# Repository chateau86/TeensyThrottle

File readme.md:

Teensy Throttle Project

4 Throttle Channels. 8 2-way switches (16 buttons). Exponentially-weighted moving average self-tuning for all analog inputs.

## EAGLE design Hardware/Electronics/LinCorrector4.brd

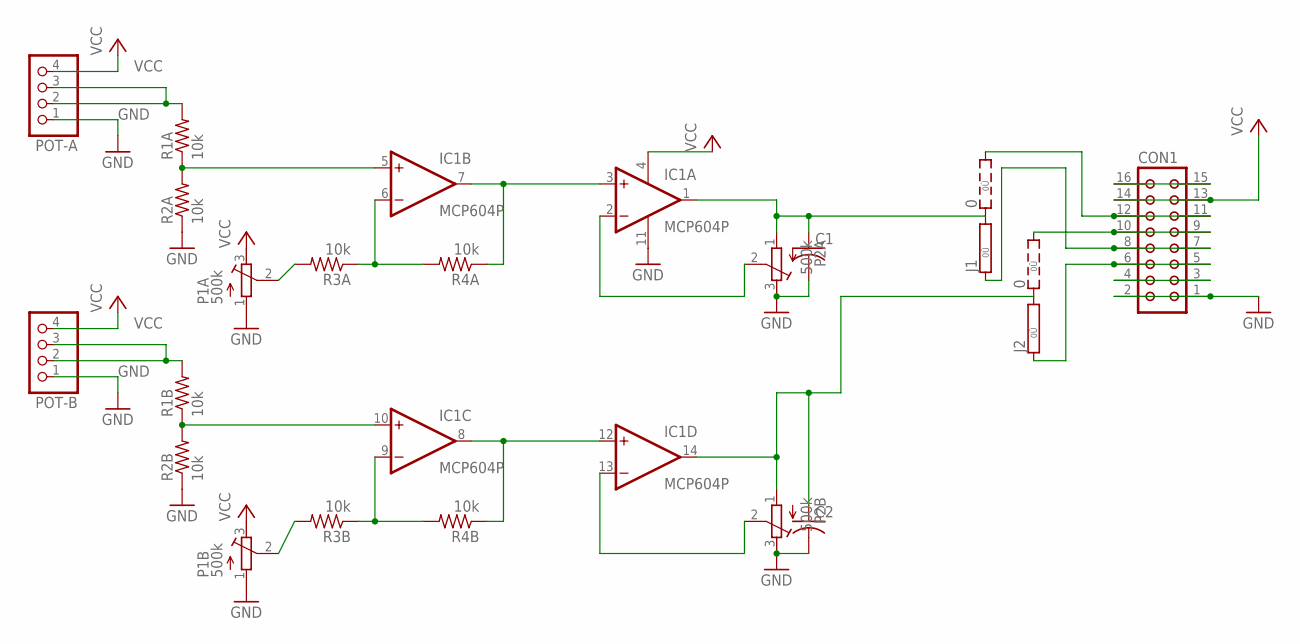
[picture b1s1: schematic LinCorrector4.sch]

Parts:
C1, C2: C-US050-030X075; C050-030X075
CON1: CON16
IC1: MCP604P; DIL14
J1, J2: 0; 0R2/10
P1A, P1B, P2A, P2B: 500k; RTRIM3296W
POT-A: PINHD-1X4/90; 1X04/90
POT-B: PINHD-1X4/90; 1X04/90
R1A, R1B, R2A, R2B, R3A, R3B, R4A, R4B: 10k; 0204/7

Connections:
GND: C1.2, C2.2, CON1.1, CON1.2, IC1.11 (V-), P1A.1 (A), P1B.1 (A), P2A.3 (E), P2B.3 (E), POT-A.1, POT-B.1, R2A.1, R2B.1
unnamed: IC1.5 (+IN), R1A.1, R2A.2
unnamed: POT-A.2, POT-A.3, R1A.2
unnamed: P1A.2 (S), R3A.2
unnamed: IC1.6 (-IN), R3A.1, R4A.2
unnamed: IC1.3 (+IN), IC1.7 (OUT), R4A.1
unnamed: IC1.10 (+IN), R1B.1, R2B.2
unnamed: IC1.2 (-IN), P2A.2 (S)
unnamed: C1.1, IC1.1 (OUT), J1.2, P2A.1 (A)
unnamed: P1B.2 (S), R3B.2
unnamed: IC1.9 (-IN), R3B.1, R4B.2
unnamed: IC1.8 (OUT), IC1.12 (+IN), R4B.1
unnamed: IC1.13 (-IN), P2B.2 (S)
unnamed: C2.1, IC1.14 (OUT), J2.2, P2B.1 (A)
unnamed: POT-B.2, POT-B.3, R1B.2
unnamed: CON1.11, CON1.12, J1.3
unnamed: CON1.9, CON1.10, J2.3
unnamed: CON1.15, CON1.16
unnamed: CON1.3, CON1.4
unnamed: CON1.7, CON1.8, J1.1
unnamed: CON1.5, CON1.6, J2.1
VCC: CON1.13, CON1.14, IC1.4 (V+), P1A.3 (E), P1B.3 (E), POT-A.4, POT-B.4

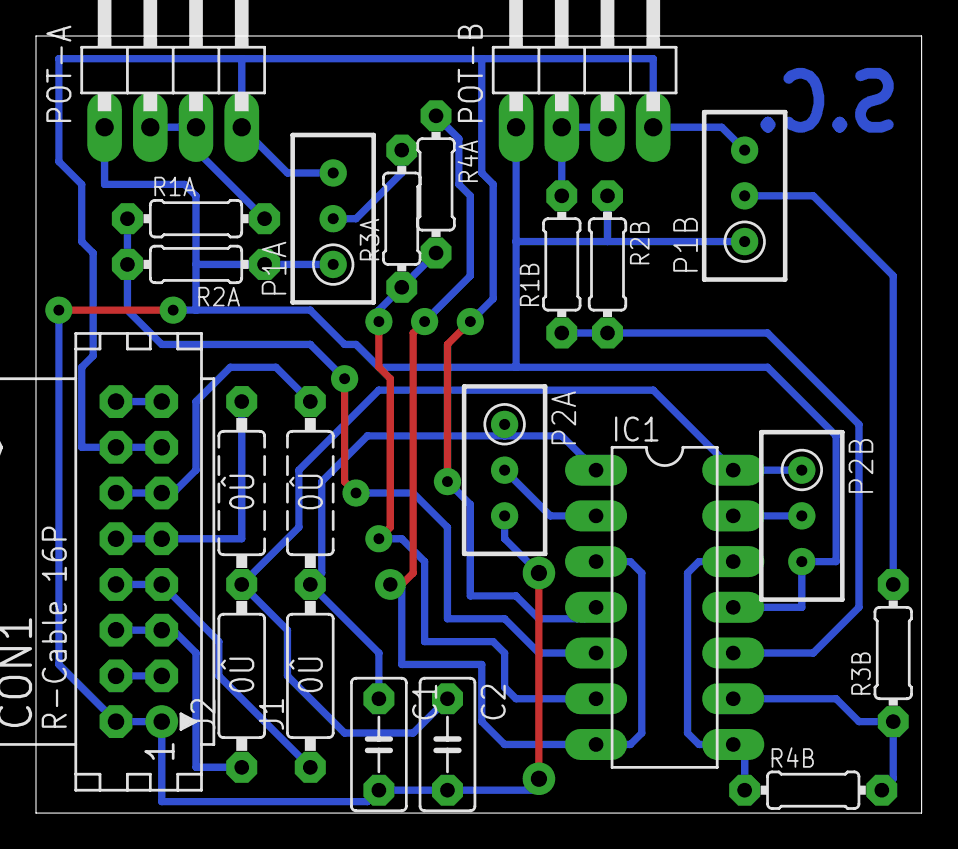
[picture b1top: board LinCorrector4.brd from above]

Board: 2 copper layers, 49.2 x 43.2 mm, 20 parts (0 on the bottom side), 22 nets.

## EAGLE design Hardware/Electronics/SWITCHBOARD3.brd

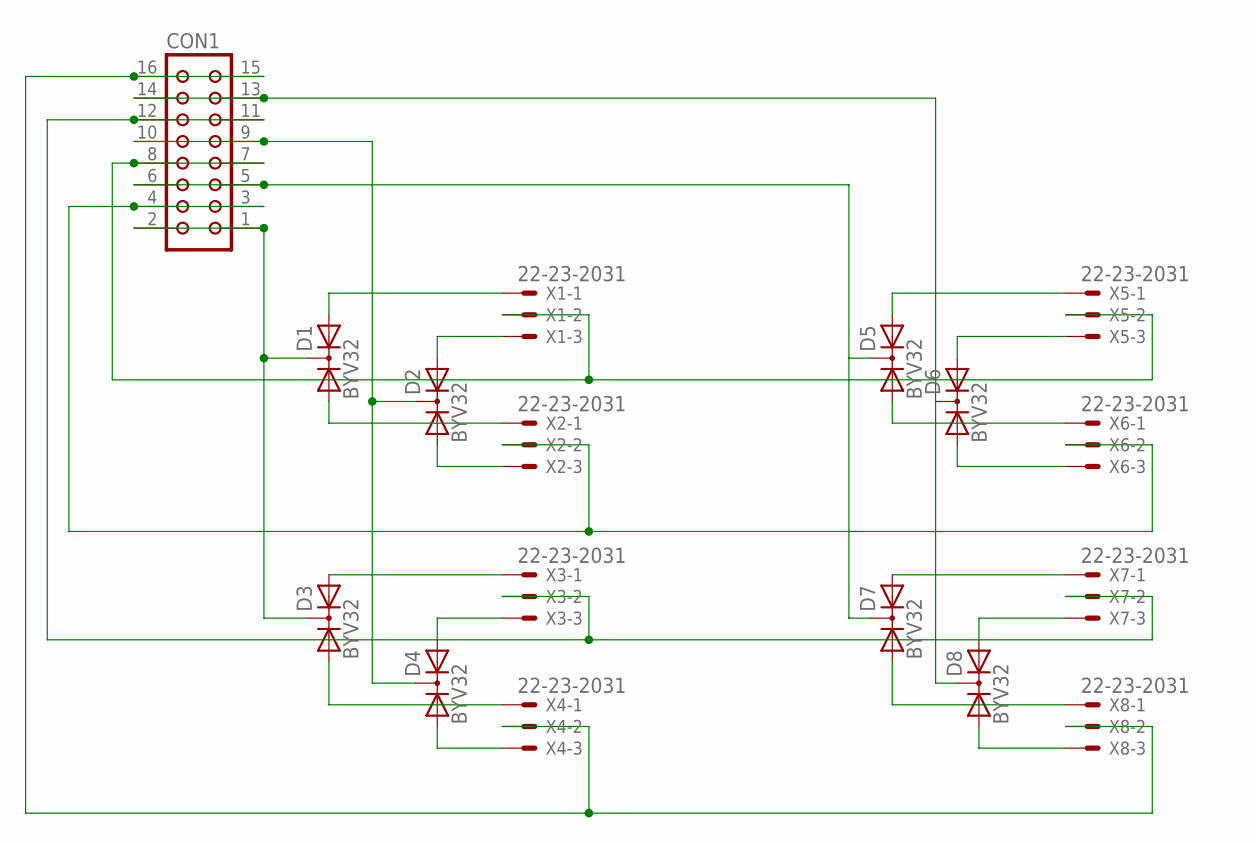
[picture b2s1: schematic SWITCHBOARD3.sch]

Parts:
CON1: CON16
D1, D2, D3, D4, D5, D6, D7, D8: BYV32; TO220ABS
X1, X2, X3, X4, X5, X6, X7, X8: 22-23-2031

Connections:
unnamed: D1.A2, X1.1
unnamed: D2.A2, X1.3
unnamed: D4.A1, X4.3
unnamed: D4.A2, X3.3
unnamed: D1.A1, X2.1
unnamed: D2.A1, X2.3
unnamed: D3.A2, X3.1
unnamed: D3.A1, X4.1
unnamed: D5.A2, X5.1
unnamed: D5.A1, X6.1
unnamed: D6.A2, X5.3
unnamed: D6.A1, X6.3
unnamed: D7.A2, X7.1
unnamed: D7.A1, X8.1
unnamed: D8.A2, X7.3
unnamed: D8.A1, X8.3
unnamed: CON1.9, CON1.10, D2.C, D4.C
unnamed: CON1.1, CON1.2, D1.C, D3.C
unnamed: CON1.13, CON1.14, D6.C, D8.C
unnamed: CON1.7, CON1.8, X1.2, X5.2
unnamed: CON1.3, CON1.4, X2.2, X6.2
unnamed: CON1.11, CON1.12, X3.2, X7.2
unnamed: CON1.15, CON1.16, X4.2, X8.2
unnamed: CON1.5, CON1.6, D5.C, D7.C

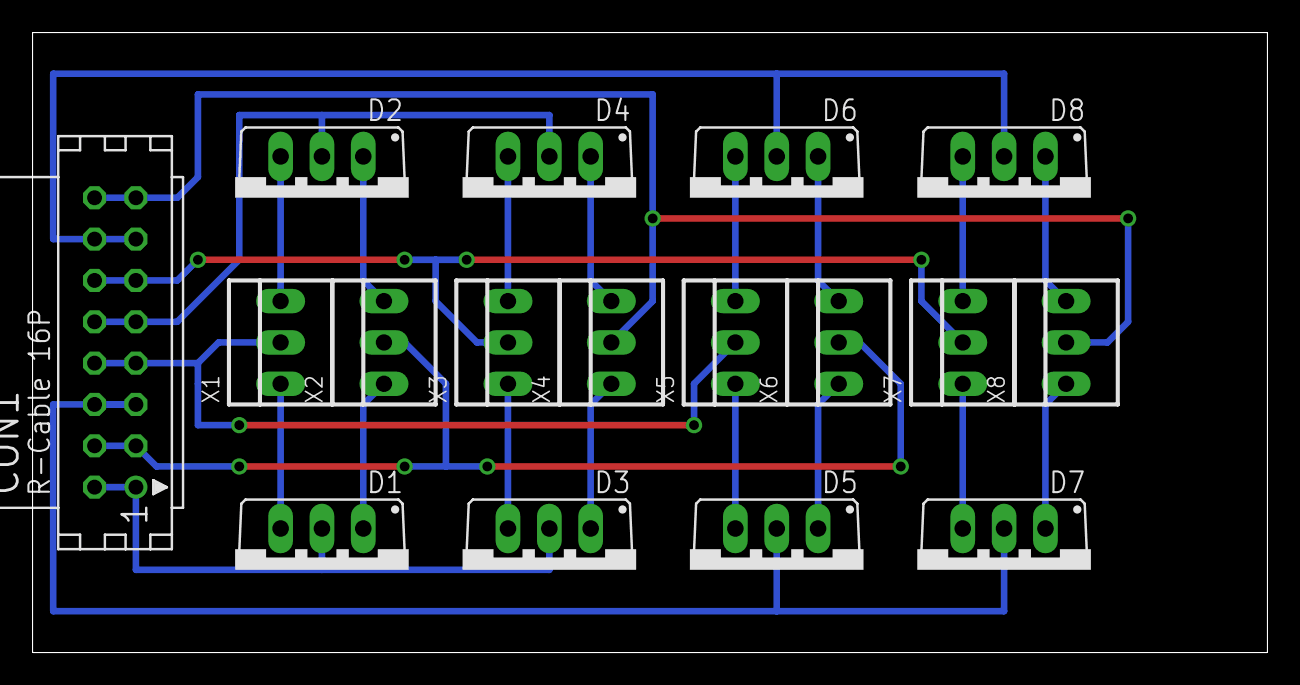
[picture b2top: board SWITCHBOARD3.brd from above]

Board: 2 copper layers, 75.9 x 38.1 mm, 17 parts (0 on the bottom side), 24 nets.

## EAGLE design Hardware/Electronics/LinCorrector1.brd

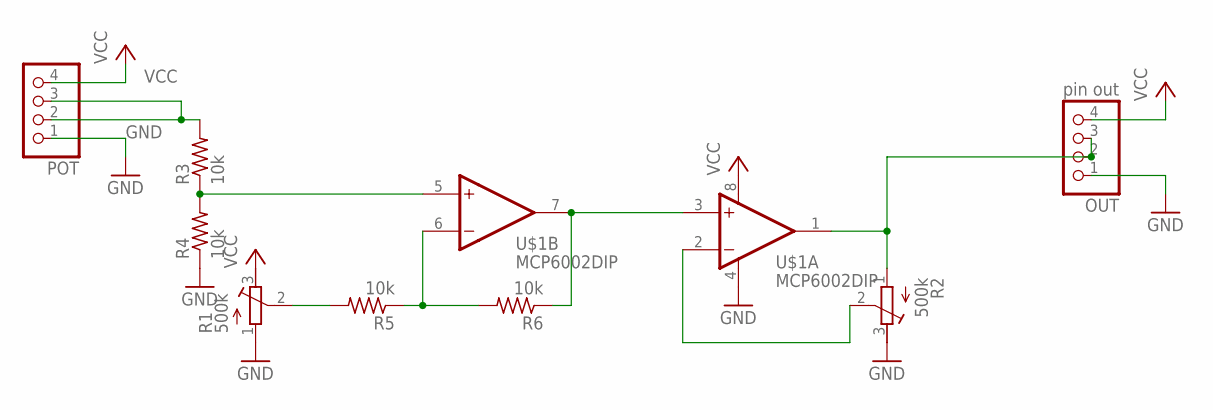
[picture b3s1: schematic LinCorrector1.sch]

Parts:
OUT: pin out; 1X04/90
POT: PINHD-1X4/90; 1X04/90
R1, R2: 500k; RTRIM3296W
R3, R4, R5, R6: 10k; 0204/7
U$1: MCP6002DIP; DIP-8

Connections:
GND: OUT.1, POT.1, R1.1 (A), R2.3 (E), R4.1, U$1.4 (V-)
unnamed: R3.1, R4.2, U$1.5 (+IN)
unnamed: POT.2, POT.3, R3.2
unnamed: R1.2 (S), R5.2
unnamed: R5.1, R6.2, U$1.6 (-IN)
unnamed: R6.1, U$1.3 (+IN), U$1.7 (OUT)
unnamed: R2.2 (S), U$1.2 (-IN)
unnamed: OUT.2, OUT.3, R2.1 (A), U$1.1 (OUT)
VCC: OUT.4, POT.4, R1.3 (E), U$1.8 (V+)

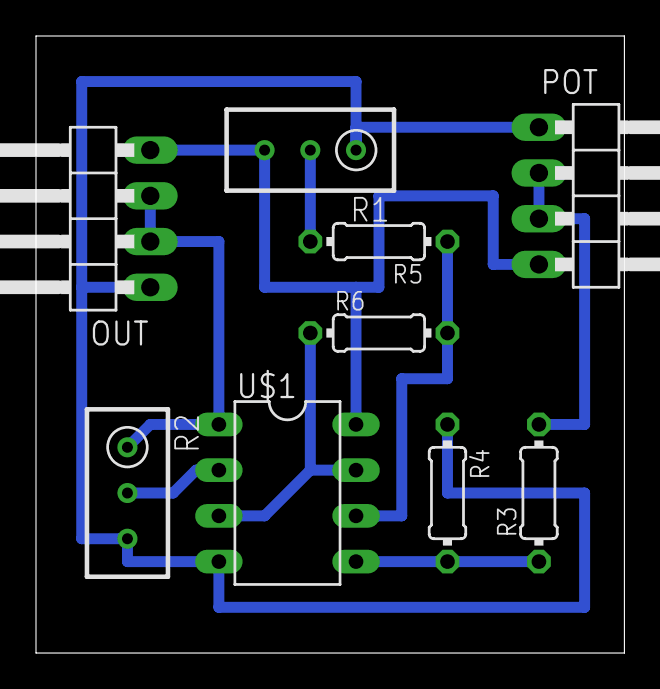
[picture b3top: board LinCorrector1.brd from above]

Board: 2 copper layers, 32.7 x 34.3 mm, 9 parts (0 on the bottom side), 9 nets.

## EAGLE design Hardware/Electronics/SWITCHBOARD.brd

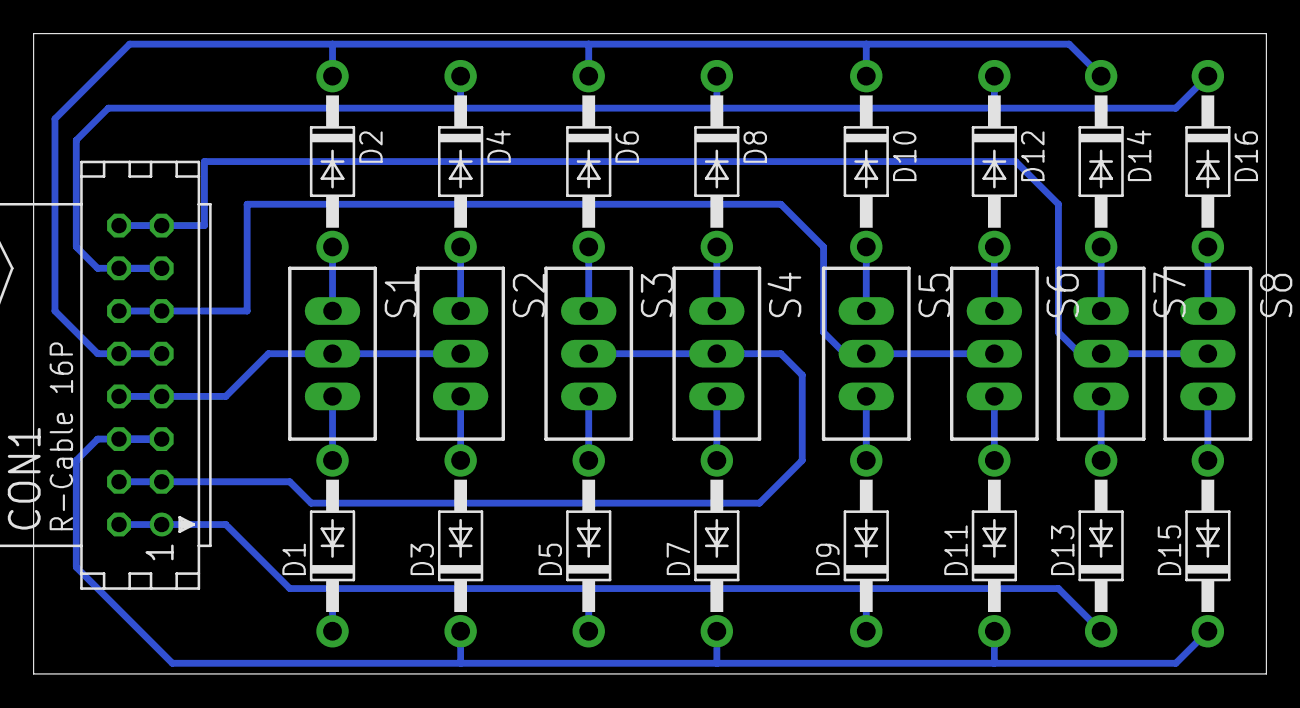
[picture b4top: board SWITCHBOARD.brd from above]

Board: 2 copper layers, 73.3 x 38.1 mm, 25 parts (0 on the bottom side), 24 nets.

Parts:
CON1: CON16
D1, D2, D3, D4, D5, D6, D7, D8, D9, D10, D11, D12, D13, D14, D15, D16: 1N4004; DO41-10
S1, S2, S3, S4, S5, S6, S7, S8: TL37PO; TL3XPO

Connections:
unnamed: D1.A, S1.3
unnamed: D2.A, S1.1
unnamed: D3.A, S2.3
unnamed: D4.A, S2.1
unnamed: D5.A, S3.3
unnamed: D6.A, S3.1
unnamed: D7.A, S4.3
unnamed: D8.A, S4.1
unnamed: D9.A, S5.3
unnamed: D10.A, S5.1
unnamed: D11.A, S6.3
unnamed: D12.A, S6.1
unnamed: D13.A, S7.3
unnamed: D14.A, S7.1
unnamed: D15.A, S8.3
unnamed: D16.A, S8.1
unnamed: CON1.9, CON1.10, D2.C, D6.C, D10.C, D14.C
unnamed: CON1.1, CON1.2, D1.C, D5.C, D9.C, D13.C
unnamed: CON1.13, CON1.14, D4.C, D8.C, D12.C, D16.C
unnamed: CON1.7, CON1.8, S1.2, S2.2
unnamed: CON1.3, CON1.4, S3.2, S4.2
unnamed: CON1.11, CON1.12, S5.2, S6.2
unnamed: CON1.15, CON1.16, S7.2, S8.2
unnamed: CON1.5, CON1.6, D3.C, D7.C, D11.C, D15.C

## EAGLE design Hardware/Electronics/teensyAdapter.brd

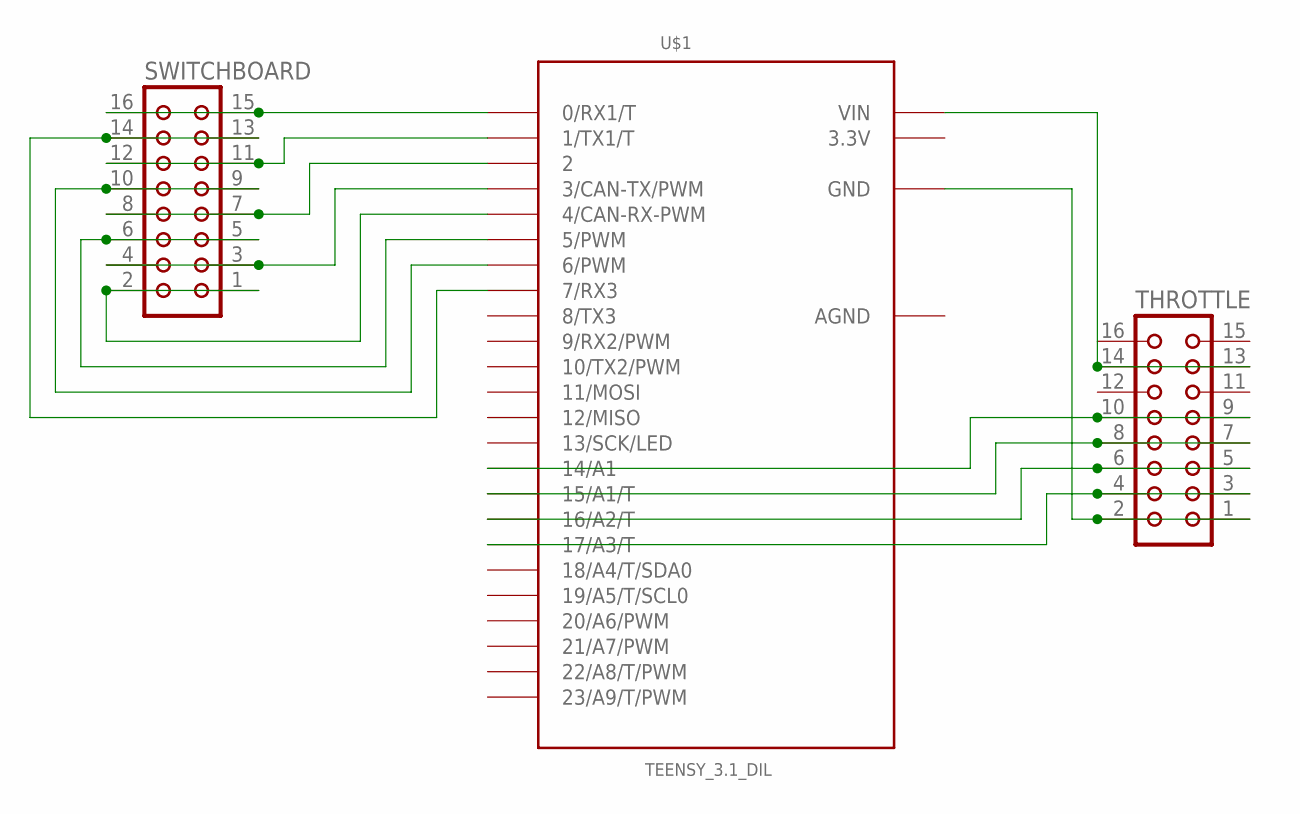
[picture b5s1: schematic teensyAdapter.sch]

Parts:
SWITCHBOARD: CON16
THROTTLE: CON16
U$1: TEENSY_3.1_DIL; TEENSY3-DIL

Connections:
3.3V: U$1.3.3V
AGND: U$1.AGND
unnamed: SWITCHBOARD.15, SWITCHBOARD.16, U$1.0 (0/RX1/T)
unnamed: SWITCHBOARD.11, SWITCHBOARD.12, U$1.1 (1/TX1/T)
unnamed: SWITCHBOARD.7, SWITCHBOARD.8, U$1.2
unnamed: SWITCHBOARD.3, SWITCHBOARD.4, U$1.3 (3/CAN-TX/PWM)
unnamed: THROTTLE.13, THROTTLE.14, U$1.VIN
unnamed: THROTTLE.1, THROTTLE.2, U$1.GND
unnamed: SWITCHBOARD.1, SWITCHBOARD.2, U$1.4 (4/CAN-RX-PWM)
unnamed: SWITCHBOARD.5, SWITCHBOARD.6, U$1.5 (5/PWM)
unnamed: SWITCHBOARD.9, SWITCHBOARD.10, U$1.6 (6/PWM)
unnamed: SWITCHBOARD.13, SWITCHBOARD.14, U$1.7 (7/RX3)
unnamed: THROTTLE.9, THROTTLE.10, U$1.14/A0 (14/A1)
unnamed: THROTTLE.7, THROTTLE.8, U$1.15/A1 (15/A1/T)
unnamed: THROTTLE.5, THROTTLE.6, U$1.16/A2 (16/A2/T)
unnamed: THROTTLE.3, THROTTLE.4, U$1.17/A3 (17/A3/T)

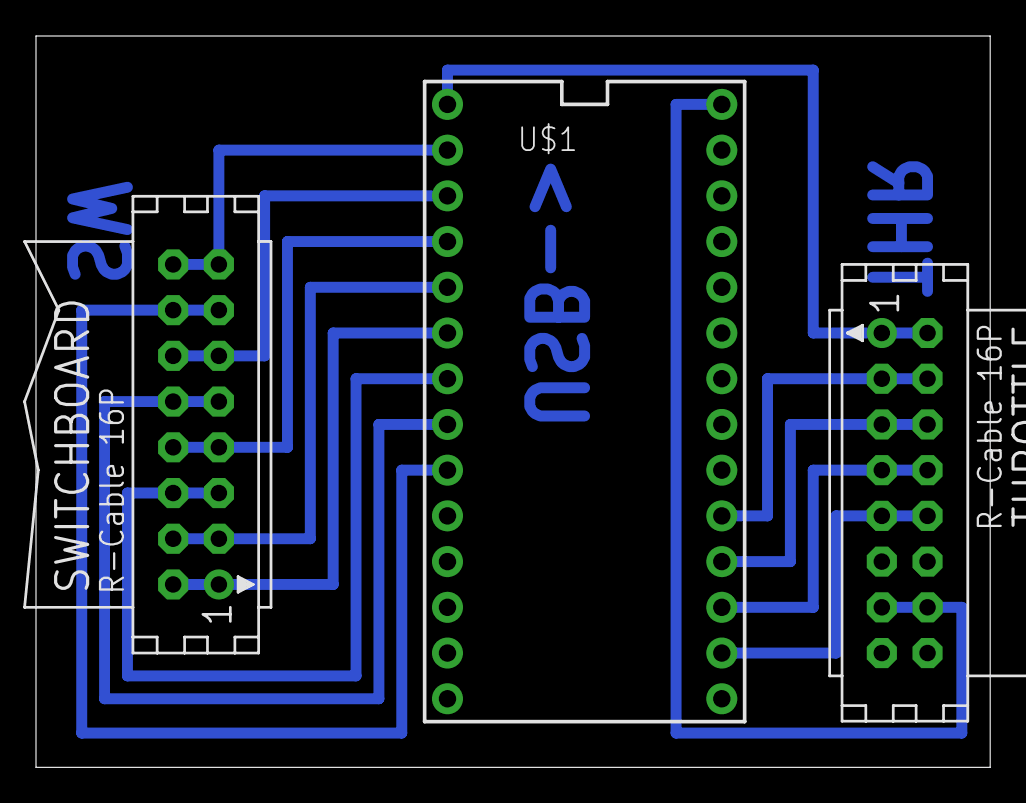
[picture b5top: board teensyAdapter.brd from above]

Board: 2 copper layers, 53.0 x 40.6 mm, 3 parts (0 on the bottom side), 14 nets.

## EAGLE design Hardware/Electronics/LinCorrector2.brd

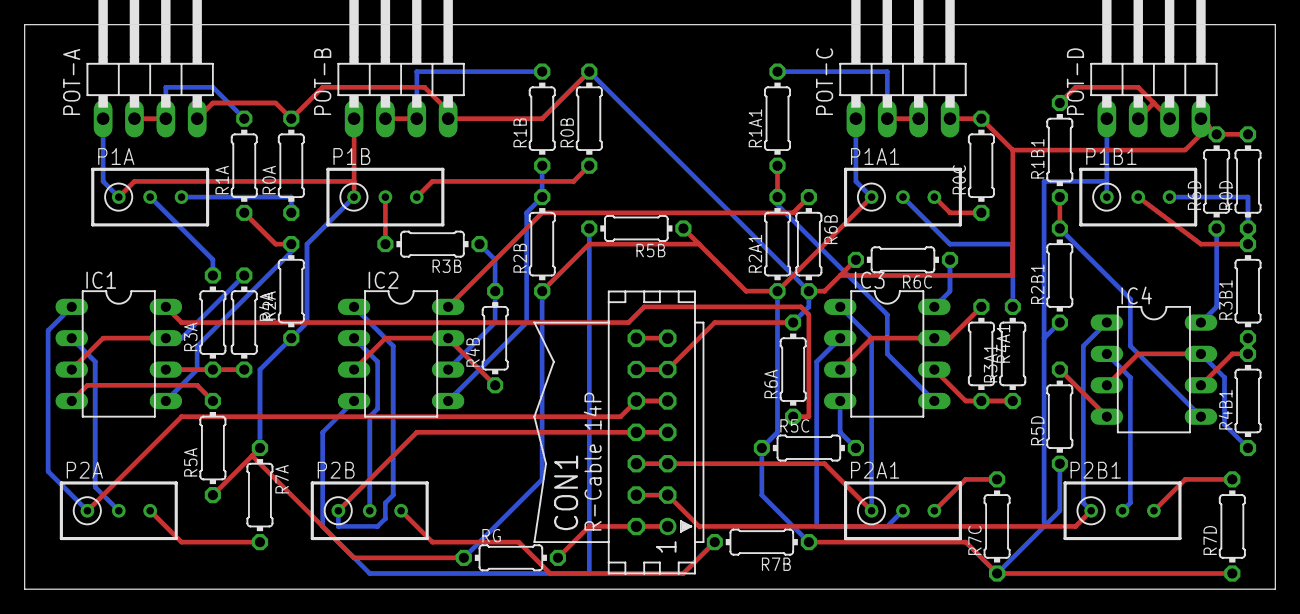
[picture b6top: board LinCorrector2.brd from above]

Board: 2 copper layers, 101.3 x 45.7 mm, 50 parts (0 on the bottom side), 48 nets.

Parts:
CON1: CON14
IC1, IC2, IC3, IC4: MCP6002DIP; DIP-8
P1A, P1A1, P1B, P1B1, P2A, P2A1, P2B, P2B1: 500k; RTRIM3296W
POT-A: 1X04/90
POT-B: 1X04/90
POT-C: 1X04/90
POT-D: 1X04/90
R0A, R0B, R0C, R0D, R5A, R5B, R5C, R5D, R6A, R6B, R6C, R6D, R7A, R7B, R7C, R7D: 0; 0204/7
R1A, R1A1, R1B, R1B1, R2A, R2A1, R2B, R2B1, R3A, R3A1, R3B, R3B1, R4A, R4A1, R4B, R4B1: 10k; 0204/7
RG: 0; 0204/7

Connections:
GND: P1A.1, P1A1.1, P1B.1, P1B1.1, POT-A.1, POT-B.1, POT-C.1, POT-D.1, R2A.1, R2A1.1, R2B.1, R2B1.1, R5A.1, R5B.1, R5C.1, R5D.1, R7A.1, R7B.1, R7C.1, R7D.1, RG.1
unnamed: IC1.5, R1A.1, R2A.2
unnamed: POT-A.2, POT-A.3, R1A.2
unnamed: P1A.2, R3A.2
unnamed: IC1.6, R3A.1, R4A.2
unnamed: IC1.3, IC1.7, R4A.1
unnamed: IC2.5, R1B.1, R2B.2
unnamed: IC1.2, P2A.2
unnamed: CON1.9, CON1.10, IC1.1, P2A.1
unnamed: P1B.2, R3B.2
unnamed: IC2.6, R3B.1, R4B.2
unnamed: IC2.3, IC2.7, R4B.1
unnamed: IC2.2, P2B.2
unnamed: CON1.7, CON1.8, IC2.1, P2B.1
unnamed: POT-B.2, POT-B.3, R1B.2
unnamed: IC3.5, R1A1.1, R2A1.2
unnamed: P1A1.2, R3A1.2
unnamed: IC3.6, R3A1.1, R4A1.2
unnamed: IC3.3, IC3.7, R4A1.1
unnamed: IC3.2, P2A1.2
unnamed: CON1.5, CON1.6, IC3.1, P2A1.1
unnamed: POT-C.2, POT-C.3, R1A1.2
unnamed: IC4.5, R1B1.1, R2B1.2
unnamed: P1B1.2, R3B1.2
unnamed: IC4.6, R3B1.1, R4B1.2
unnamed: IC4.3, IC4.7, R4B1.1
unnamed: IC4.2, P2B1.2
unnamed: P1A.3, R0A.1
unnamed: POT-D.2, POT-D.3, R1B1.2
unnamed: CON1.3, CON1.4, IC4.1, P2B1.1
unnamed: P1B.3, R0B.1
unnamed: P1A1.3, R0C.1
unnamed: P1B1.3, R0D.1
unnamed: IC1.8, R6A.1
unnamed: IC1.4, R5A.2
unnamed: IC2.8, R6B.1
unnamed: IC3.8, R6C.1
unnamed: IC4.8, R6D.1
unnamed: IC2.4, R5B.2
unnamed: IC3.4, R5C.2
unnamed: IC4.4, R5D.2
unnamed: P2A.3, R7A.2
unnamed: P2B.3, R7B.2
unnamed: P2A1.3, R7C.2
unnamed: P2B1.3, R7D.2
unnamed: CON1.1, CON1.2, RG.2
unnamed: CON1.13, CON1.14
VCC: CON1.11, CON1.12, POT-A.4, POT-B.4, POT-C.4, POT-D.4, R0A.2, R0B.2, R0C.2, R0D.2, R6A.2, R6B.2, R6C.2, R6D.2

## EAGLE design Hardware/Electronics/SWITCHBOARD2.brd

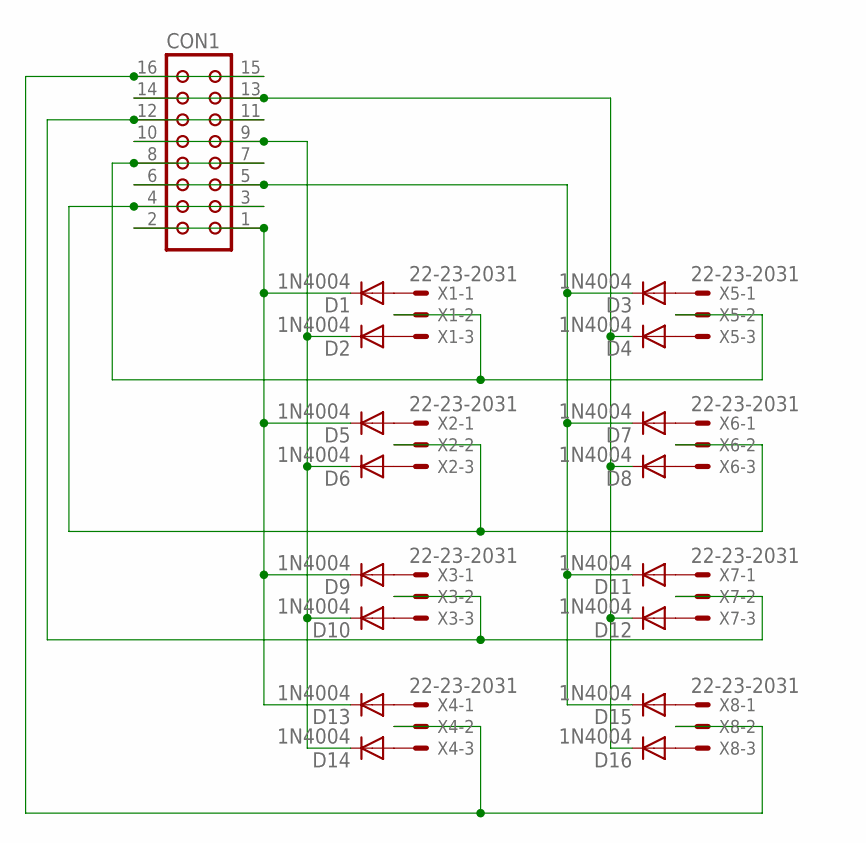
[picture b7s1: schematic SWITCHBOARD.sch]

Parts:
CON1: CON16
D1, D2, D3, D4, D5, D6, D7, D8, D9, D10, D11, D12, D13, D14, D15, D16: 1N4004; DO41-10
X1, X2, X3, X4, X5, X6, X7, X8: 22-23-2031

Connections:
unnamed: D1.A, X1.1
unnamed: D2.A, X1.3
unnamed: D3.A, X5.1
unnamed: D4.A, X5.3
unnamed: D5.A, X2.1
unnamed: D6.A, X2.3
unnamed: D7.A, X6.1
unnamed: D8.A, X6.3
unnamed: D9.A, X3.1
unnamed: D10.A, X3.3
unnamed: D11.A, X7.1
unnamed: D12.A, X7.3
unnamed: D13.A, X4.1
unnamed: D14.A, X4.3
unnamed: D15.A, X8.1
unnamed: D16.A, X8.3
unnamed: CON1.9, CON1.10, D2.C, D6.C, D10.C, D14.C
unnamed: CON1.1, CON1.2, D1.C, D5.C, D9.C, D13.C
unnamed: CON1.13, CON1.14, D4.C, D8.C, D12.C, D16.C
unnamed: CON1.7, CON1.8, X1.2, X5.2
unnamed: CON1.3, CON1.4, X2.2, X6.2
unnamed: CON1.11, CON1.12, X3.2, X7.2
unnamed: CON1.15, CON1.16, X4.2, X8.2
unnamed: CON1.5, CON1.6, D3.C, D7.C, D11.C, D15.C

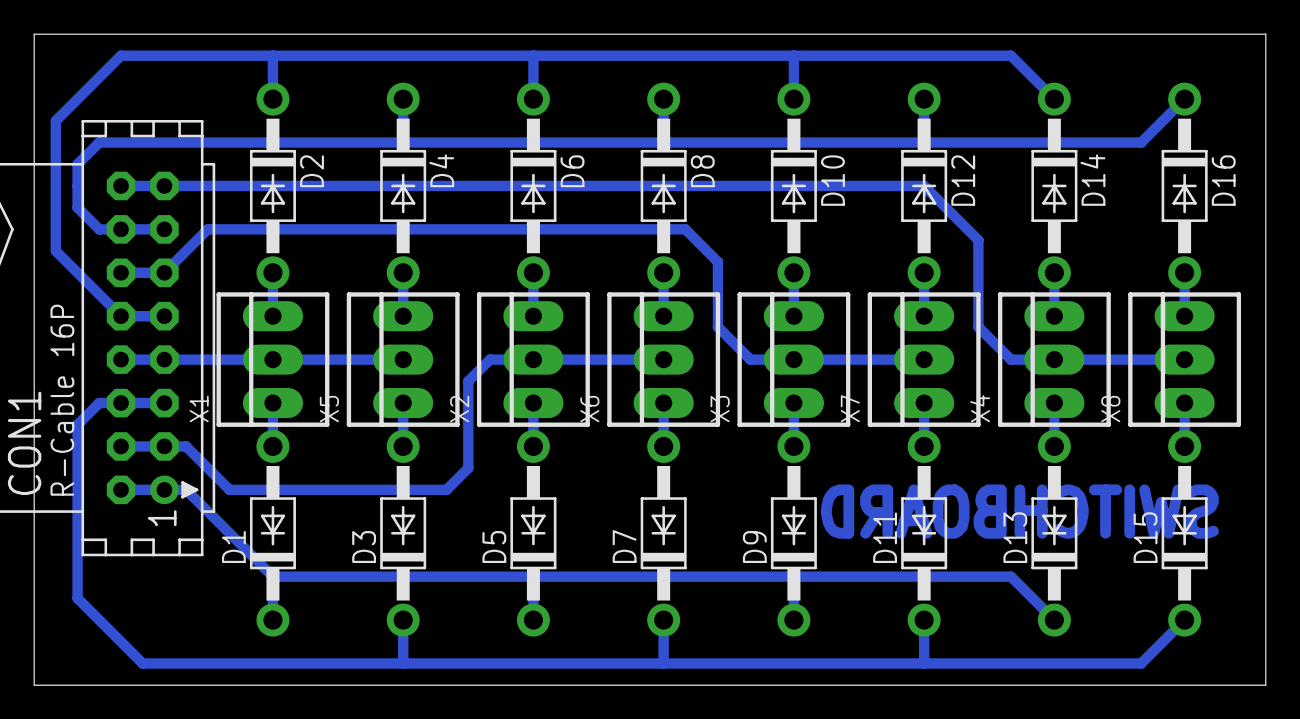
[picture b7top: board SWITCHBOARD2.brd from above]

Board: 2 copper layers, 72.1 x 38.1 mm, 25 parts (0 on the bottom side), 24 nets.

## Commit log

2017-07-15 Initial seed commit of existing code.
2017-07-15 Updated readme.
2017-07-15 More readme update.
